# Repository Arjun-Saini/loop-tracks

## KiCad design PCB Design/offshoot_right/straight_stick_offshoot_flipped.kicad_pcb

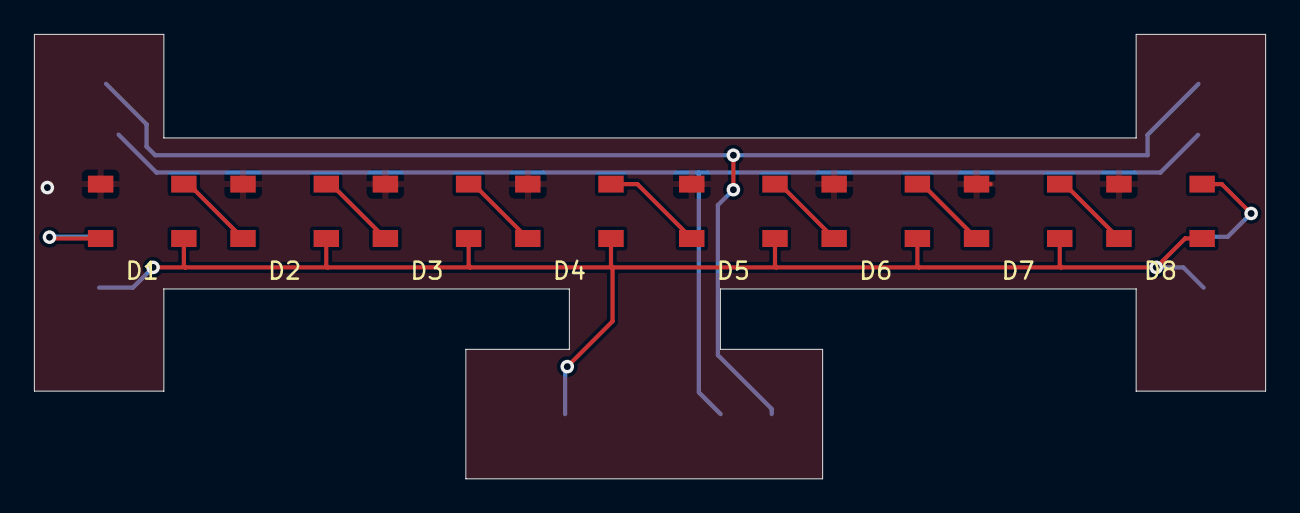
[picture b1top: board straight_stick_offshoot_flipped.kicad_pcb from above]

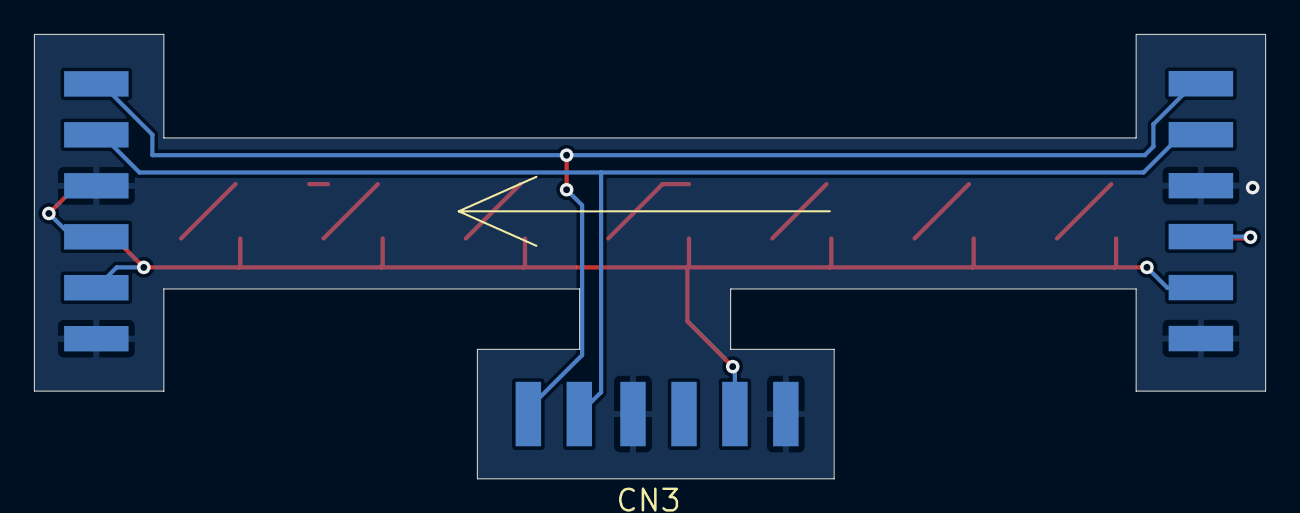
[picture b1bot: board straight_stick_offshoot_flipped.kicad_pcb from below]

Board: 2 copper layers, 72.5 x 26.2 mm, 11 parts (3 on the bottom side), 13 nets.

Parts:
CN1, CN2, CN3: 1X4SMT; 1X4-SMT
D1, D2, D3, D4, D5, D6, D7, D8: WS2812B; LED_WS2812B_PLCC4_5.0x5.0mm_P3.2mm

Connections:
+5V: CN1.5, CN2.2, CN3.5, D1.1 (VDD), D2.1 (VDD), D3.1 (VDD), D4.1 (VDD), D5.1 (VDD), D6.1 (VDD), D7.1 (VDD), D8.1 (VDD)
GND: CN1.3, CN1.6, CN2.1, CN2.4, CN3.3, CN3.6, D1.3 (VSS), D2.3 (VSS), D3.3 (VSS), D4.3 (VSS), D5.3 (VSS), D6.3 (VSS), D7.3 (VSS), D8.3 (VSS)
unnamed: CN1.1, CN2.6, CN3.1
unnamed: CN1.2, CN2.5, CN3.2
unnamed: CN1.4, D8.2 (DOUT)
unnamed: CN2.3, D1.4 (DIN)
unnamed: D1.2 (DOUT), D2.4 (DIN)
unnamed: D2.2 (DOUT), D3.4 (DIN)
unnamed: D3.2 (DOUT), D4.4 (DIN)
unnamed: D4.2 (DOUT), D5.4 (DIN)
unnamed: D5.2 (DOUT), D6.4 (DIN)
unnamed: D6.2 (DOUT), D7.4 (DIN)
unnamed: D7.2 (DOUT), D8.4 (DIN)

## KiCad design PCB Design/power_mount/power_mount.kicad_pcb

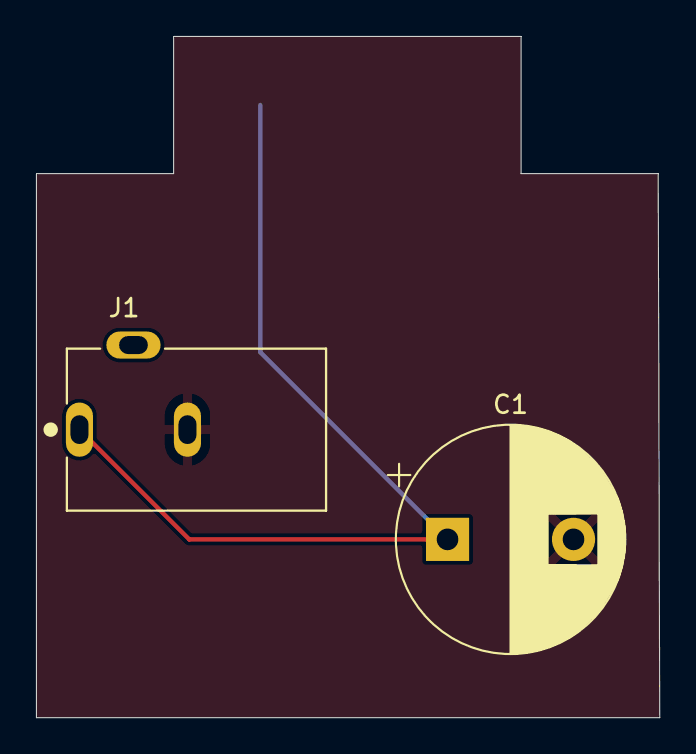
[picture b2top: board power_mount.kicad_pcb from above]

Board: 2 copper layers, 34.6 x 37.8 mm, 3 parts (1 on the bottom side), 2 nets.

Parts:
C1: C_Polarized; CP_Radial_D12.5mm_P6.00mm
CN2: 1X4SMT; 1X4-SMT
J1: PJ-102AH

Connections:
+5V: C1.1, CN2.2, J1.1
GND: C1.2, CN2.1, CN2.4, J1.2

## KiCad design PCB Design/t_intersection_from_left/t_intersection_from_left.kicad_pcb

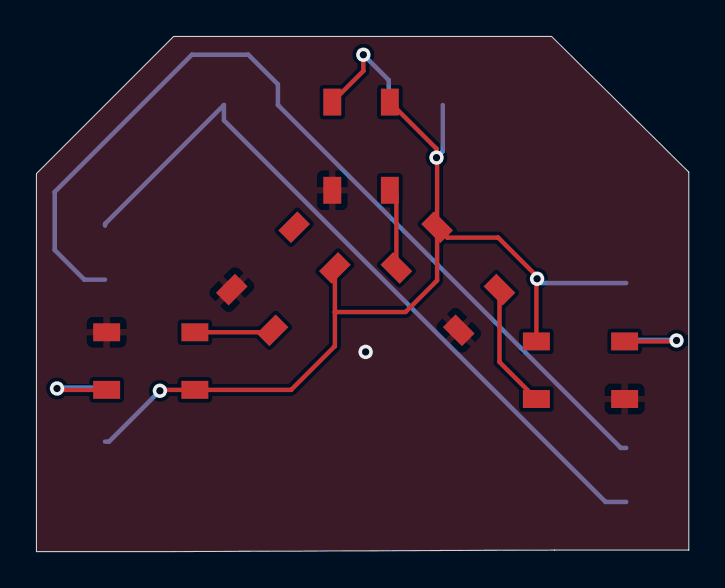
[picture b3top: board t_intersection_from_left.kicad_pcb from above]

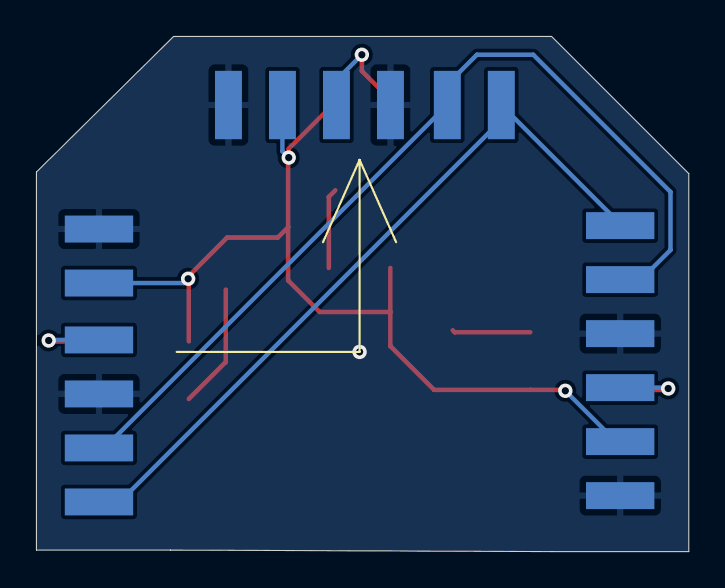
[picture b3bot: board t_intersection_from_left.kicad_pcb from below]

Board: 2 copper layers, 36.2 x 28.6 mm, 8 parts (3 on the bottom side), 10 nets.

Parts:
CN1, CN2, CN3: 1X4SMT; 1X4-SMT
D1, D2, D3, D4, D5: WS2812B; LED_WS2812B_PLCC4_5.0x5.0mm_P3.2mm

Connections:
+5V: CN1.5, CN2.2, CN3.2, D1.1 (VDD), D2.1 (VDD), D3.1 (VDD), D4.1 (VDD), D5.1 (VDD)
GND: CN1.3, CN1.6, CN2.1, CN2.4, CN3.1, CN3.4, D1.3 (VSS), D2.3 (VSS), D3.3 (VSS), D4.3 (VSS), D5.3 (VSS)
unnamed: CN1.1, CN2.6, CN3.6
unnamed: CN1.2, CN2.5, CN3.5
unnamed: CN1.4, D3.2 (DOUT)
unnamed: CN2.3, D1.4 (DIN)
unnamed: CN3.3, D4.4 (DIN)
unnamed: D1.2 (DOUT), D2.4 (DIN)
unnamed: D2.2 (DOUT), D3.4 (DIN)
unnamed: D4.2 (DOUT), D5.4 (DIN)
